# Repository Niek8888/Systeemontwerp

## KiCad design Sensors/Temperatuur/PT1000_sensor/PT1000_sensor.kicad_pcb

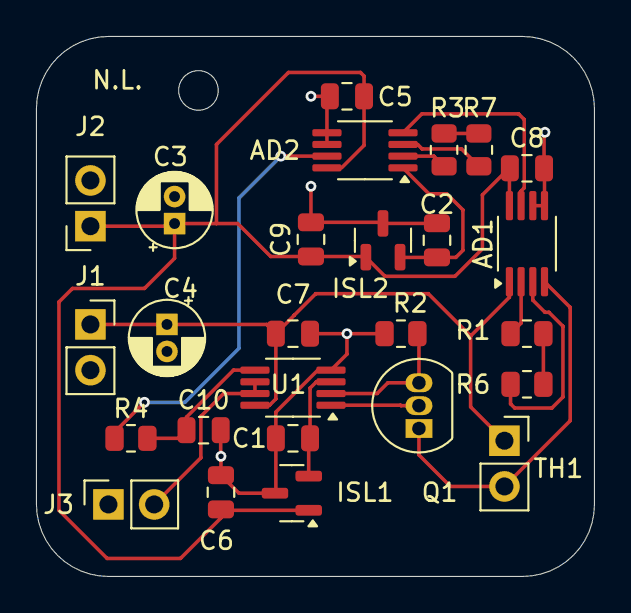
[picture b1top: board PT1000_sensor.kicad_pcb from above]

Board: 2 copper layers, 31.0 x 30.0 mm, 26 parts (0 on the bottom side), 18 nets.

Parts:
AD1, AD2: MSOP-8_3x3mm_P0.65mm
C1, C2: 1nF; C_0805_2012Metric
C3, C4: 10uF; CP_Radial_D4.0mm_P1.50mm
C5: 100nf; C_0805_2012Metric
C6, C7, C8, C9, C10: 100nF; C_0805_2012Metric
ISL1: 1.024; SOT-23
ISL2: 2.048; SOT-23
J1, J2, J3: Conn_01x02_Pin; PinSocket_1x02_P2.54mm_Vertical
Q1: BC546; TO-92_Inline
R1: 910; R_0805_2012Metric
R2: 24k; R_0805_2012Metric
R3: 16k; R_0805_2012Metric
R4: 160K; R_0805_2012Metric
R6: 62; R_0805_2012Metric
R7: 510; R_0805_2012Metric
TH1: PT1000; PinSocket_1x02_P2.54mm_Vertical
U1: LTC2055; MSOP-8_3x3mm_P0.65mm

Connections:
+1.024V: C1.1, ISL1.2 (OUT), U1.3 (+)
+2.048V: AD2.1 (-), C2.1, ISL2.2 (OUT)
+3.3V: AD1.1 (-), C4.1, C7.1, J2.1, TH1.1, U1.8 (V+)
+5V: AD1.8 (Vs+), AD2.8 (Vs+), C3.1, C5.1, C6.1, C8.1, C9.1, ISL1.1 (IN), ISL2.1 (IN), J1.1
/-V_s: AD1.4 (+), Q1.1 (C), TH1.2
GND: AD1.5 (Vs-), AD1.6 (Ref), AD2.5 (Vs-), AD2.6 (Ref), C1.2, C2.2, C3.2, C4.2, C5.2, C6.2, C7.2, C8.2, C9.2, C10.2, ISL1.3 (GND), ISL2.3 (GND), J1.2, J2.2, J3.1, R2.2, U1.4 (V-)
unnamed: AD1.2 (Rg), R1.2
unnamed: AD1.3 (Rg), R6.2
unnamed: AD1.7, AD2.4 (+)
unnamed: AD2.7, R4.1
unnamed: AD2.2 (Rg), R3.2
unnamed: AD2.3 (Rg), R7.2
unnamed: J3.2, U1.6 (-), U1.7
unnamed: Q1.2 (B), U1.1
unnamed: Q1.3 (E), R2.1, U1.2 (-)
unnamed: R1.1, R6.1
unnamed: R3.1, R7.1
unnamed: C10.1, R4.2, U1.5 (+)

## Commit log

2024-09-04 voordelen van titanium en wat er nog bij moet
2024-09-04 update text file
2024-09-04 new file structer
2024-09-05 versterker eisen opgesteld grof
2024-09-05 added specs
2024-09-09 added systeemontwerp file
2024-09-09 systeemontwerp onderbouwt
2024-09-09 luchtvochtigheid ideeen
2024-09-09 versterker voor temperatuur beetje genoteerd
2024-09-09 git ignore file
2024-09-09 update specs
2024-09-29 new schematics for presentation
2024-09-30 resistor value for amplifer first stage
2024-09-30 added a matlab file to calculate the noise
2024-09-30 added an if boom
2024-09-30 added a test file to learn octave
2024-10-03 calculated the noise of opamp need current noise
2024-10-03 added stash
2024-10-03 added back the AD8220 noise calculations
2024-10-04 did the noise calculations for the current source and first stage amplifer
2024-10-05 Added the second opamp in noise calculations
2024-10-06 added kicad schematic and updated octave calculations
2024-10-07 created a pcb and sends it of
2024-10-07 changed the noise integral because the specs of the sensor are lower than expected
2024-10-09 finished pcb and updated schematics
2024-10-13 added ltspice simulations and update noise cal for new opamps
2024-10-14 made a way to cut the power to the AD8226
2024-10-14 a added the all R values for the Pt1000
2024-10-14 added Pt1000 instead of R
2024-10-15 made some new schematics
2024-10-22 added new features for evaulation
2024-10-24 added some new drawio figures
2024-10-24 merged with arch side of laptop
2024-11-11 added some schematics and the latex file
2024-11-27 added a local latex project
